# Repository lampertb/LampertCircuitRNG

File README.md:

Lampert Circuit Hardware Files

This repository holds the hardware design files for the Stanford Lampert Circuit Random Number Generator Circuit.

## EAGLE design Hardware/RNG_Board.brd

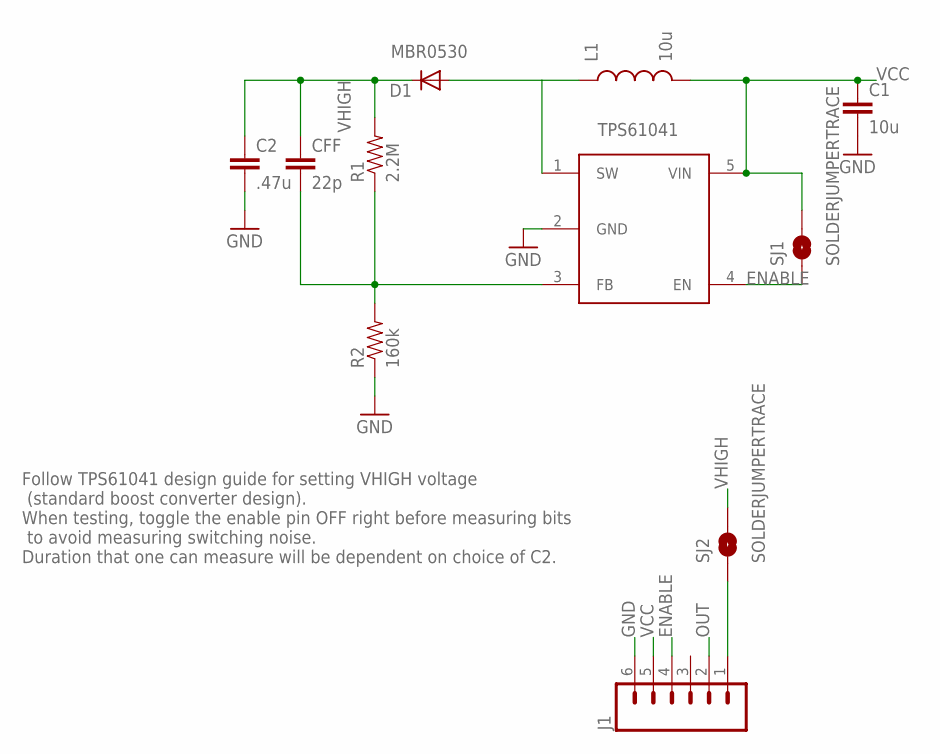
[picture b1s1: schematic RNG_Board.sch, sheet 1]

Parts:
C1: 10u; 0603-CAP
C2: .47u; 0603-CAP
CFF: 22p; 0603-CAP
D1: MBR0530; SOD-123_MINI-SMA
J1: M06SILK_FEMALE_PTH; 1X06
L1: 10u; 0805
R1: 2.2M; 0603-RES
R2: 160k; 0603-RES
SJ1, SJ2: SOLDERJUMPERTRACE; SJ_2S-TRACE
U$1: TPS61040; SOT23-5

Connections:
ENABLE: J1.4, SJ1.1, U$1.4 (EN)
GND: C1.2, C2.2, J1.6, R2.1, U$1.2 (GND); also elsewhere on the board
unnamed: CFF.2, R1.1, R2.2, U$1.3 (FB)
unnamed: D1.A, L1.1, U$1.1 (SW)
unnamed: J1.1, SJ2.1
OUT: J1.2; also elsewhere on the board
VCC: C1.1, J1.5, L1.2, SJ1.2, U$1.5 (VIN); also elsewhere on the board
VHIGH: C2.1, CFF.1, D1.C, R1.2, SJ2.2; also elsewhere on the board

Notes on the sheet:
TPS61041
Follow TPS61041 design guide for setting VHIGH voltage (standard boost converter design). When testing, toggle the enable pin OFF right before measuring bits to avoid measuring switching noise. Duration that one can measure will be dependent on choice of C2.

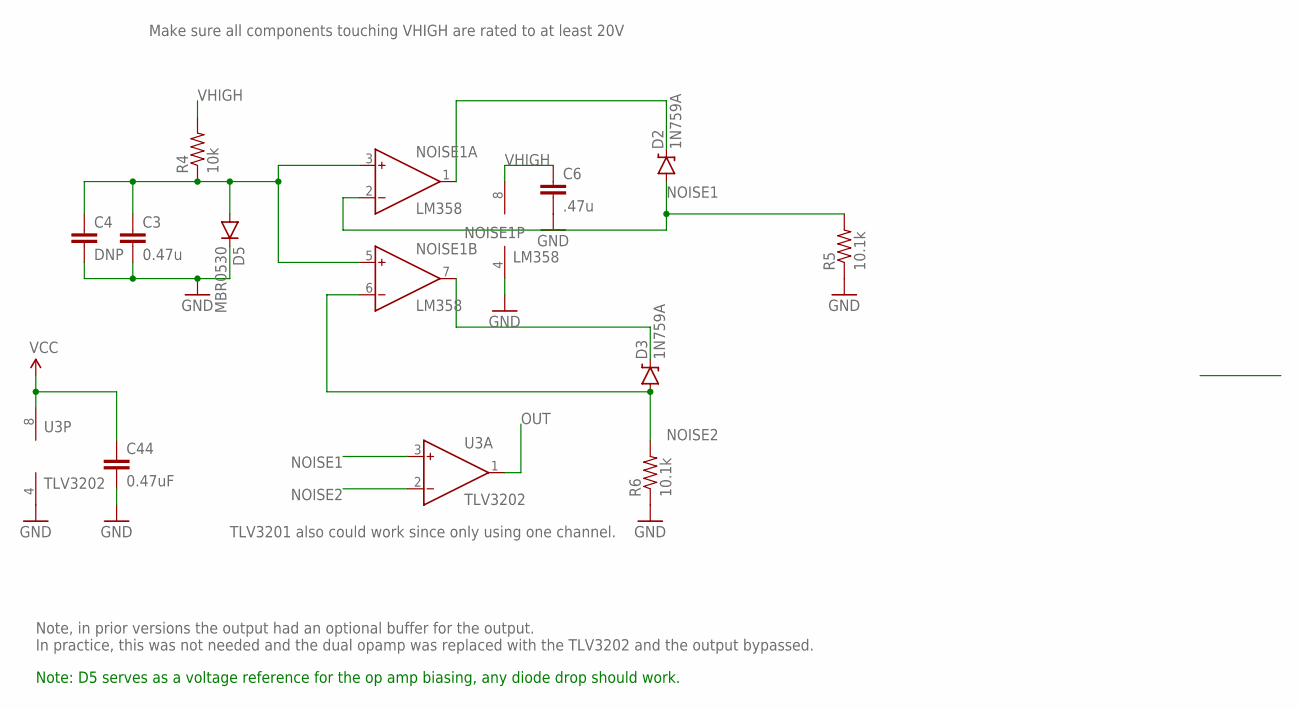
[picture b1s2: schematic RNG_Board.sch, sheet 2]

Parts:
C3: 0.47u; 0603-CAP
C4: DNP; 0603-CAP
C6: .47u; 0603-CAP
C44: 0.47uF; C0603
D2, D3: 1N759A; DIODE-ZENER; MPN 610-1N759A
D5: MBR0530; SOD-123
NOISE1: LM358; SO8
R4: 10k; 0603-RES
R5, R6: 10.1k; 0603-RES
U3: TLV3202; SO8

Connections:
GND: C3.2, C4.2, C6.2, C44.2, D5.C, NOISE1.4 (V-), R5.1, R6.1, U3.4 (V-); also elsewhere on the board
unnamed: D2.P$1 (C), NOISE1.1 (OUT)
unnamed: D3.P$1 (C), NOISE1.7 (OUT)
unnamed: C3.1, C4.1, D5.A, NOISE1.3 (IN+), NOISE1.5 (IN+), R4.1
NOISE1: D2.P$2 (A), NOISE1.2 (IN-), R5.2, U3.3 (IN+)
NOISE2: D3.P$2 (A), NOISE1.6 (IN-), R6.2, U3.2 (IN-)
OUT: U3.1 (OUT); also elsewhere on the board
VCC: C44.1, U3.8 (V+); also elsewhere on the board
VHIGH: C6.1, NOISE1.8 (V+), R4.2; also elsewhere on the board

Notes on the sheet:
Make sure all components touching VHIGH are rated to at least 20V
Note, in prior versions the output had an optional buffer for the output. In practice, this was not needed and the dual opamp was replaced with the TLV3202 and the output bypassed.
TLV3201 also could work since only using one channel.
Note: D5 serves as a voltage reference for the op amp biasing, any diode drop should work.

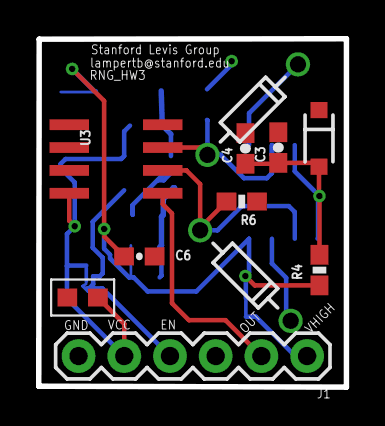
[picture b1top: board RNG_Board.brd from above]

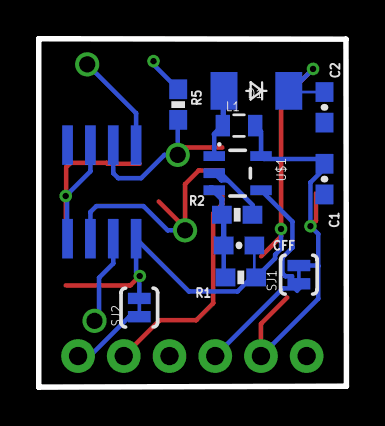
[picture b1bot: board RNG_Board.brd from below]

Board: 2 copper layers, 17.1 x 19.4 mm, 23 parts (12 on the bottom side), 13 nets.

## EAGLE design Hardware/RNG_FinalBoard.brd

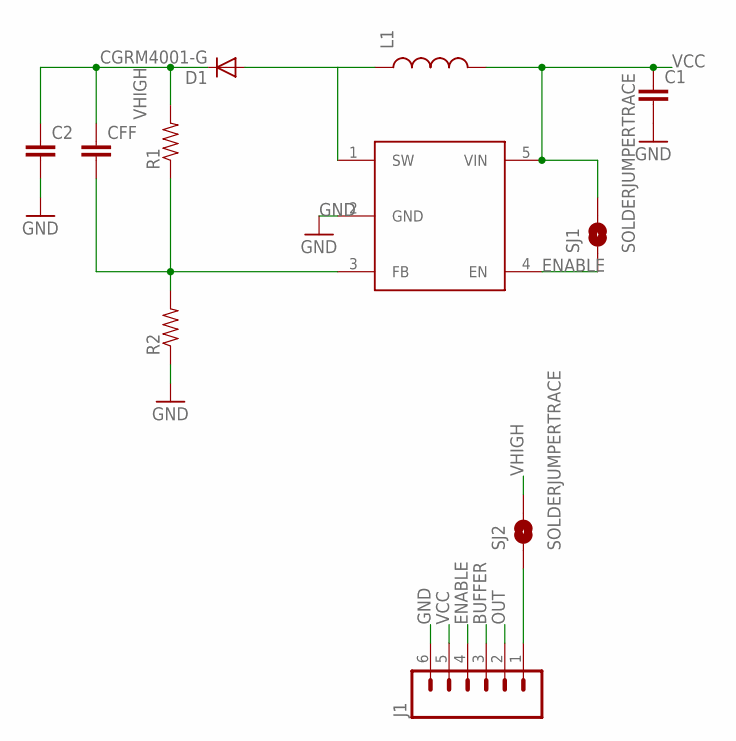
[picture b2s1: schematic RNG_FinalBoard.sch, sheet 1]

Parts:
C1, C2: CAP0603-CAP; 0603-CAP
CFF: CAP0603-CAP; 0603-CAP
D1: CGRM4001-G; SOD-123_MINI-SMA
J1: M06SILK_FEMALE_PTH; 1X06
L1: INDUCTOR0805; 0805
R1, R2: 0.27OHM-1/10W-1%(0603); 0603-RES
SJ1, SJ2: SOLDERJUMPERTRACE; SJ_2S-TRACE
U$1: TPS61040; SOT23-5

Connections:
BUFFER: J1.3; also elsewhere on the board
ENABLE: J1.4, SJ1.1, U$1.4 (EN)
GND: C1.2, J1.6, R2.1, U$1.2 (GND); also elsewhere on the board
unnamed: CFF.2, R1.1, R2.2, U$1.3 (FB)
unnamed: D1.A, L1.1, U$1.1 (SW)
unnamed: J1.1, SJ2.1
OUT: J1.2; also elsewhere on the board
VCC: C1.1, J1.5, L1.2, SJ1.2, U$1.5 (VIN); also elsewhere on the board
VHIGH: C2.1, CFF.1, D1.C, R1.2, SJ2.2; also elsewhere on the board

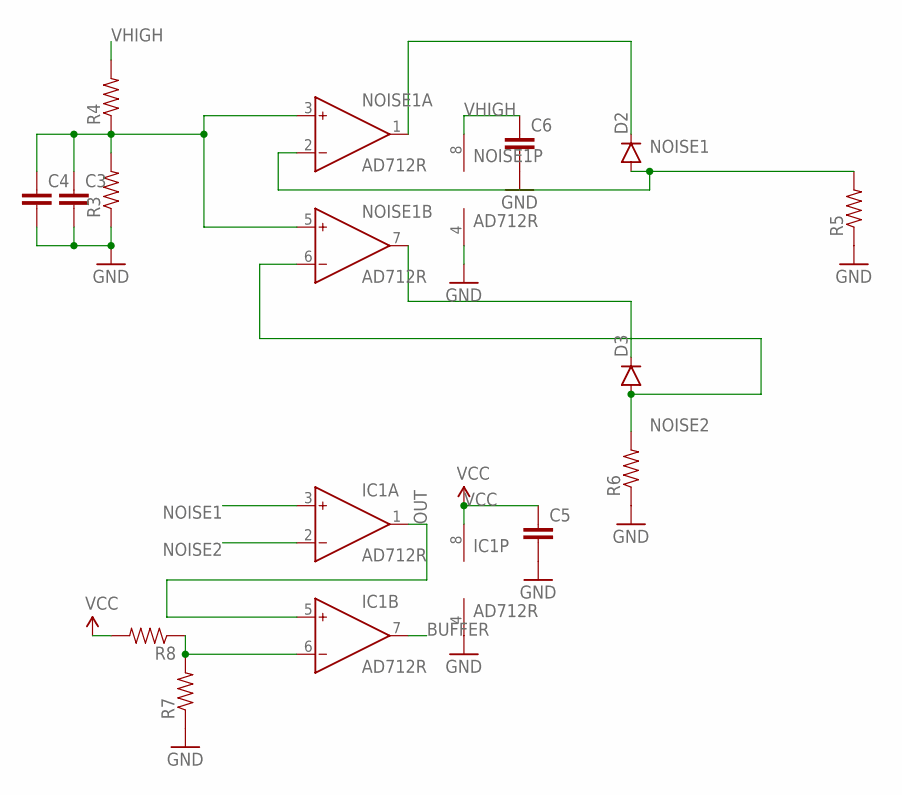
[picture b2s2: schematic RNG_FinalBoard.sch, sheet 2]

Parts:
C3, C4, C5, C6: CAP0603-CAP; 0603-CAP
D2, D3: DIODESOD523; SOD523
IC1: AD712R; SO8
NOISE1: AD712R; SO8
R3, R4, R5, R6: RESISTOR0603; 0603-RES
R7, R8: RESISTOR0603-RES; 0603-RES

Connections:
BUFFER: IC1.7 (OUT); also elsewhere on the board
GND: C3.2, C4.2, C5.2, C6.2, IC1.4 (V-), NOISE1.4 (V-), R3.1, R5.1, R6.1, R7.1; also elsewhere on the board
unnamed: D2.C, NOISE1.1 (OUT)
unnamed: D3.C, NOISE1.7 (OUT)
unnamed: IC1.6 (IN-), R7.2, R8.1
unnamed: C3.1, C4.1, NOISE1.3 (IN+), NOISE1.5 (IN+), R3.2, R4.1
NOISE1: D2.A, IC1.3 (IN+), NOISE1.2 (IN-), R5.2
NOISE2: D3.A, IC1.2 (IN-), NOISE1.6 (IN-), R6.2
OUT: IC1.1 (OUT), IC1.5 (IN+); also elsewhere on the board
VCC: C5.1, IC1.8 (V+), R8.2; also elsewhere on the board
VHIGH: C6.1, NOISE1.8 (V+), R4.2; also elsewhere on the board

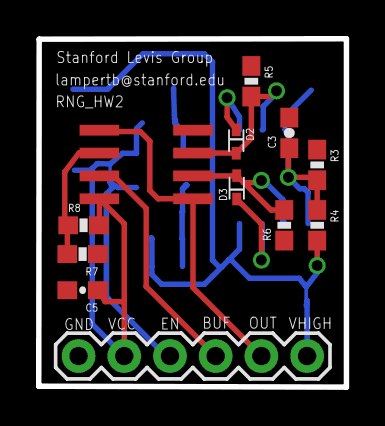
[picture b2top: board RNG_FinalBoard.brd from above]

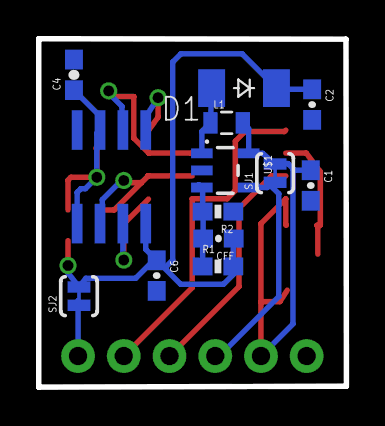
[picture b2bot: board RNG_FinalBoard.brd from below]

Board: 2 copper layers, 17.1 x 19.4 mm, 25 parts (13 on the bottom side), 15 nets.

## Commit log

2016-09-06 Added hardware eagle files
2019-09-23 Updated design to reflect imix design
    Updates:
    -Changed Zener diode to use 1N759A which is the diode used in the imix design
    -Added BOM file
    -Dropped buffer output (not needed in design)
    -Layout changes

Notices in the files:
parts and their libraries:
SparkFun-Capacitors: Licensing: Creative Commons ShareAlike 4.0 International - https://creativecommons.org/licenses/by-sa/4.0
